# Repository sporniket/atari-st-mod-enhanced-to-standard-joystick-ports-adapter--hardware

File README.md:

# Enhanced to standard joystick ports adapter -- the hardware

> [WARNING] Please read carefully this note before using this project. It contains important facts.

Content

1. What is **Enhanced to standard joystick ports adapter -- the hardware**, and when to use it ?
2. What should you know before using **Enhanced to standard joystick ports adapter -- the hardware** ?
3. How to use **Enhanced to standard joystick ports adapter -- the hardware** ?
4. Known issues
5. Miscellanous

## 1. What is **Enhanced to standard joystick ports adapter -- the hardware**, and when to use it ?

**Enhanced to standard joystick ports adapter -- the hardware**, as the name implies, is the hardware part of an adapter
that will allow to plug into the pair of standard joystick ports of an Atari ST, a controller meant for the enhanced joystick
port, like the Atari Jaguar controller.

The Kicad 6 project details the schematic and the PCB of the adapter.

### Licence

**Enhanced to standard joystick ports adapter -- the hardware** is published under the Creative Commons CC0 license. You can find a copy of the licence there : https://creativecommons.org/publicdomain/zero/1.0/legalcode

You can copy, modify, distribute and perform the work, even for commercial purposes, all without asking permission.

**Enhanced to standard joystick ports adapter -- the hardware** is distributed in the hope that it will be useful, but WITHOUT ANY WARRANTY; without even the implied warranty of MERCHANTABILITY or FITNESS FOR A PARTICULAR PURPOSE.

### Release notes

> No releases yet

## 2. What should you know before using **Enhanced to standard joystick ports adapter -- the hardware** ?

**Enhanced to standard joystick ports adapter -- the hardware** is made using Kicad 6.

> Do not use **Enhanced to standard joystick ports adapter -- the hardware** if this project is not suitable for your project.

## 3. How to use **Enhanced to standard joystick ports adapter -- the hardware** ?

### From sources

To get the latest available work, one must clone the git repository, build and install the package.

	git clone https://github.com/sporniket/atari-st-mod-enhanced-to-standard-joystick-ports-adapter--hardware.git

Then, open the project with Kicad 6.

## 4. Known issues
See the [project issues](https://github.com/sporniket/atari-st-mod-enhanced-to-standard-joystick-ports-adapter--hardware/issues) page.

## 5. Miscellanous

### Report issues
Use the [project issues](https://github.com/sporniket/atari-st-mod-enhanced-to-standard-joystick-ports-adapter--hardware/issues) page.

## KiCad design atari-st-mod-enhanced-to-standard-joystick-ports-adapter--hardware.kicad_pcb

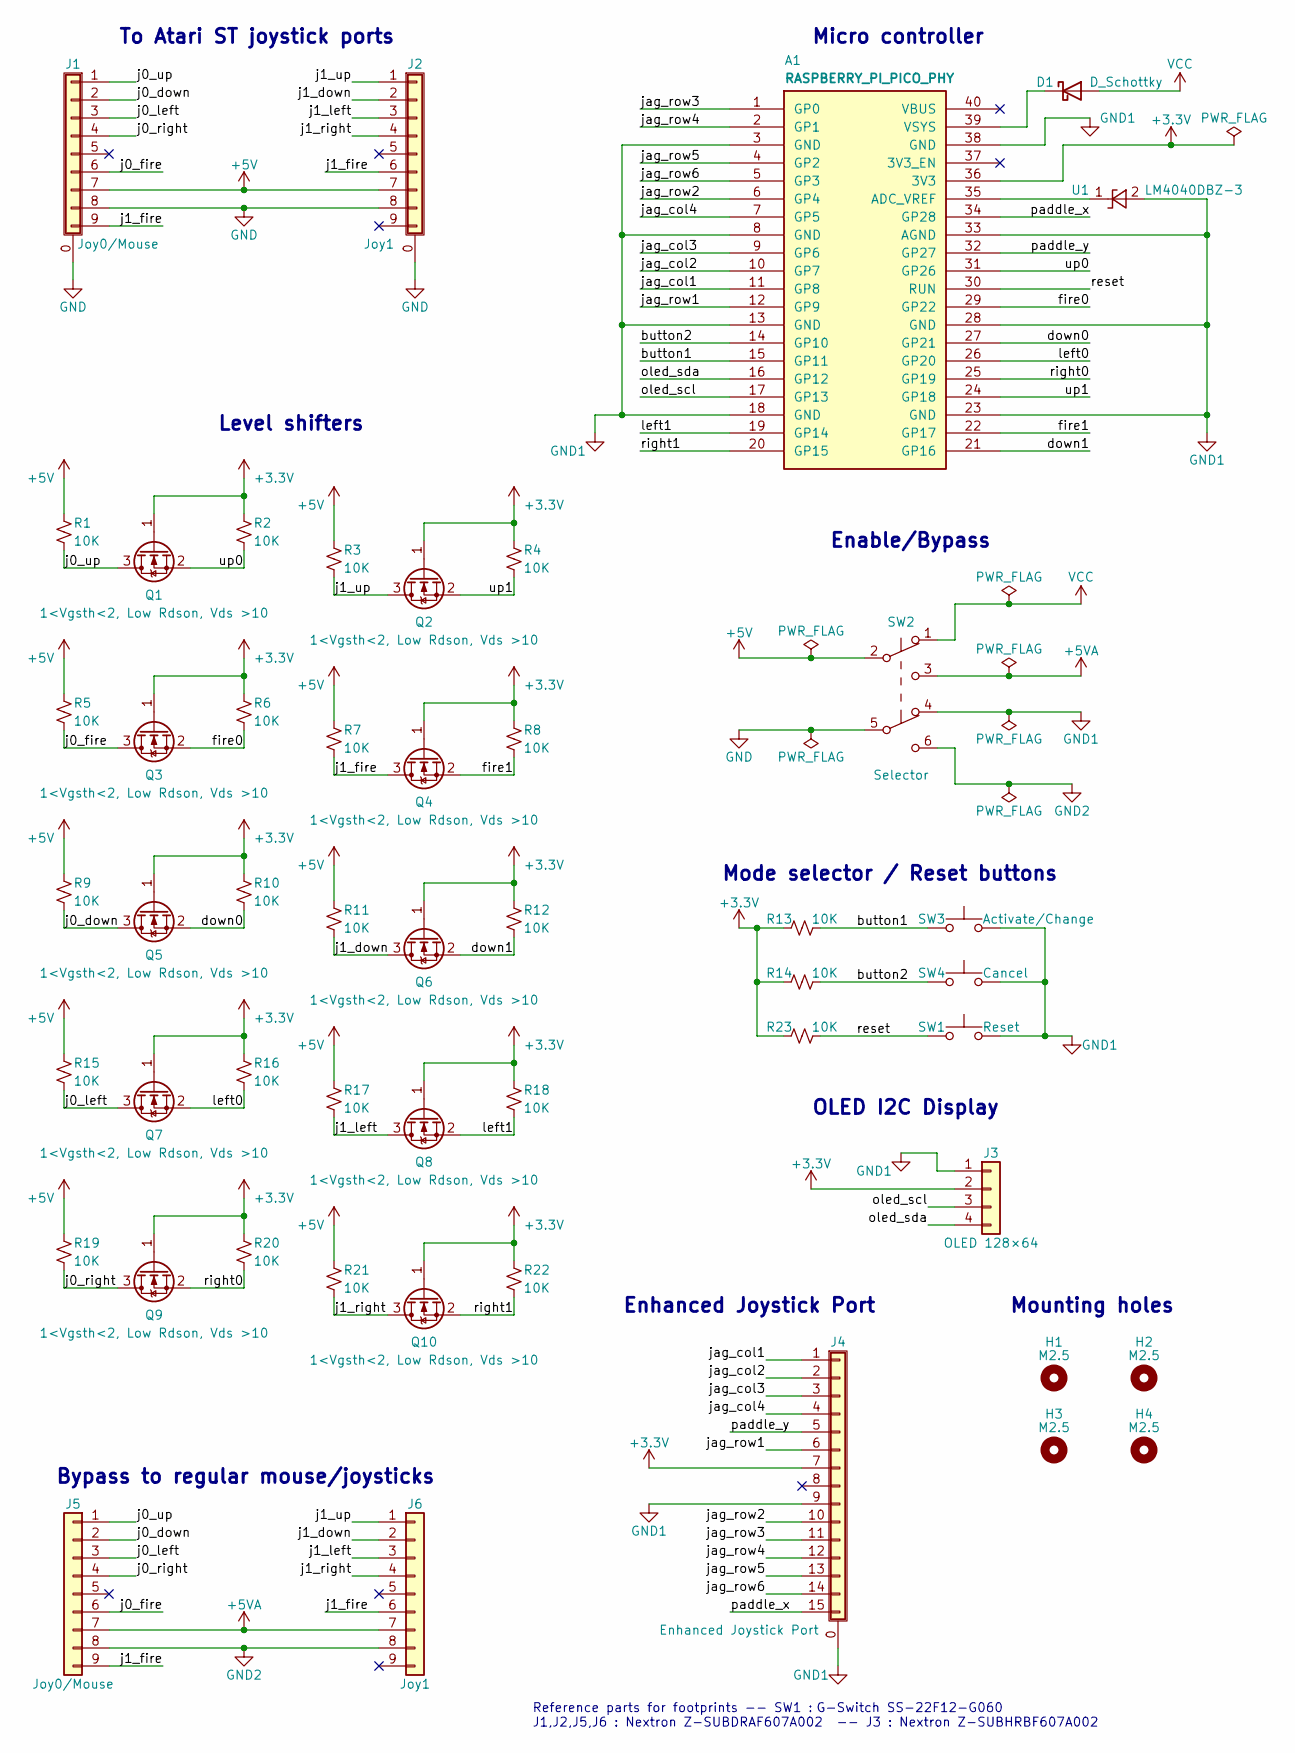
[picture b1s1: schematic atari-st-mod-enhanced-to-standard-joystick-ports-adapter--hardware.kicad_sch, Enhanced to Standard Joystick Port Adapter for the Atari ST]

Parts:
A1: RASPBERRY_PI_PICO_PHY; DIP-40_700_RASPBERRY_PI_PICO
D1: D_Schottky; D_SOD-323
H1, H2, H3, H4: M2.5; MountingHole_2.7mm_M2.5
J1: Joy0/Mouse; DSUB-9_Female_Horizontal_P2.77x2.84mm_EdgePinOffset7.70mm_H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; LCSC part number C115167
J2: Joy1; DSUB-9_Female_Horizontal_P2.77x2.84mm_EdgePinOffset7.70mm_H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; LCSC part number C115167
J3: OLED 128×64; oled_display_iic_128x64pix__outer_26.70x19.26mm__inner_21.7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
J4: Enhanced Joystick Port; DSUB-15-HD_Female_Horizontal_P2.29x1.98mm_EdgePinOffset8.35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; LCSC part number C235848
J5: Joy0/Mouse; Joystick_Port_DSUB-9_Male_Horizontal_P2.77x2.84mm_EdgePinOf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; LCSC part number C115167
J6: Joy1; Joystick_Port_DSUB-9_Male_Horizontal_P2.77x2.84mm_EdgePinOf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; LCSC part number C115167
Q1, Q2, Q3, Q4, Q5, Q6, Q7, Q8, Q9, Q10: 1<Vgsth<2, Low Rdson, Vds >10; SOT-23
R1, R2, R3, R4, R5, R6, R7, R8, R9, R10, R11, R12, R13, R14, R15, R16, R17, R18, R19, R20, R21, R22, R23: 10K; R_0805_2012Metric
SW1: Reset; SW_PUSH_6mm_H9.5mm
SW2: Selector; g-switch_22f12-gxxx; LCSC part number C2848906
SW3: Activate/Change; SW_PUSH_6mm_H13mm
SW4: Cancel; SW_PUSH_6mm_H13mm
U1: LM4040DBZ-3; SOT-23

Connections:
+3V3: A1.36 (3V3), J3.2, J4.7, Q1.1 (G), Q2.1 (G), Q3.1 (G), Q4.1 (G), Q5.1 (G), Q6.1 (G), Q7.1 (G), Q8.1 (G), Q9.1 (G), Q10.1 (G), R2.1, R4.1, R6.1, R8.1, R10.1, R12.1, R13.1, R14.1, R16.1, R18.1, R20.1, R22.1, R23.1
+5V: J1.7, J2.7, R1.1, R3.1, R5.1, R7.1, R9.1, R11.1, R15.1, R17.1, R19.1, R21.1, SW2.2 (B)
+5VA: J5.7, J6.7, SW2.3 (C)
/button1: A1.15 (GP11), R13.2, SW3.1
/button2: A1.14 (GP10), R14.2, SW4.1
/down0: A1.27 (GP21), Q5.2 (S), R10.2
/down1: A1.21 (GP16), Q6.2 (S), R12.2
/fire0: A1.29 (GP22), Q3.2 (S), R6.2
/fire1: A1.22 (GP17), Q4.2 (S), R8.2
/j0_down: J1.2, J5.2, Q5.3 (D), R9.2
/j0_fire: J1.6, J5.6, Q3.3 (D), R5.2
/j0_left: J1.3, J5.3, Q7.3 (D), R15.2
/j0_right: J1.4, J5.4, Q9.3 (D), R19.2
/j0_up: J1.1, J5.1, Q1.3 (D), R1.2
/j1_down: J2.2, J6.2, Q6.3 (D), R11.2
/j1_fire: J1.9, J2.6, J5.9, J6.6, Q4.3 (D), R7.2
/j1_left: J2.3, J6.3, Q8.3 (D), R17.2
/j1_right: J2.4, J6.4, Q10.3 (D), R21.2
/j1_up: J2.1, J6.1, Q2.3 (D), R3.2
/jag_col1: A1.11 (GP8), J4.1
/jag_col2: A1.10 (GP7), J4.2
/jag_col3: A1.9 (GP6), J4.3
/jag_col4: A1.7 (GP5), J4.4
/jag_row1: A1.12 (GP9), J4.6
/jag_row2: A1.6 (GP4), J4.10
/jag_row3: A1.1 (GP0), J4.11
/jag_row4: A1.2 (GP1), J4.12
/jag_row5: A1.4 (GP2), J4.13
/jag_row6: A1.5 (GP3), J4.14
/left0: A1.26 (GP20), Q7.2 (S), R16.2
/left1: A1.19 (GP14), Q8.2 (S), R18.2
/oled_scl: A1.17 (GP13), J3.3
/oled_sda: A1.16 (GP12), J3.4
/paddle_x: A1.34 (GP28), J4.15
/paddle_y: A1.32 (GP27), J4.5
/reset: A1.30 (RUN), R23.2, SW1.1
/right0: A1.25 (GP19), Q9.2 (S), R20.2
/right1: A1.20 (GP15), Q10.2 (S), R22.2
/up0: A1.31 (GP26), Q1.2 (S), R2.2
/up1: A1.24 (GP18), Q2.2 (S), R4.2
GND: J1.0 (Shield), J1.8, J2.0 (Shield), J2.8, SW2.5 (B)
GND1: A1.3 (GND), A1.8 (GND), A1.13 (GND), A1.18 (GND), A1.23 (GND), A1.28 (GND), A1.33 (AGND), A1.38 (GND), J3.1, J4.0 (Shield), J4.9, SW1.2, SW2.4 (A), SW3.2, SW4.2, U1.2 (A)
GND2: J5.8, J6.8, SW2.6 (C)
unnamed: A1.35 (ADC_VREF), U1.1 (K)
unnamed: A1.39 (VSYS), D1.1 (K)
VCC: D1.2 (A), SW2.1 (A)

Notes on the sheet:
To Atari ST joystick ports
Level shifters
Bypass to regular mouse/joysticks
Mounting holes
Micro controller
OLED I2C Display
Enable/Bypass
Mode selector / Reset buttons
Enhanced Joystick Port
Reference parts for footprints -- SW1 : G-Switch SS-22F12-G060 J1,J2,J5,J6 : Nextron Z-SUBDRAF607A002 -- J3 : Nextron Z-SUBHRBF607A002

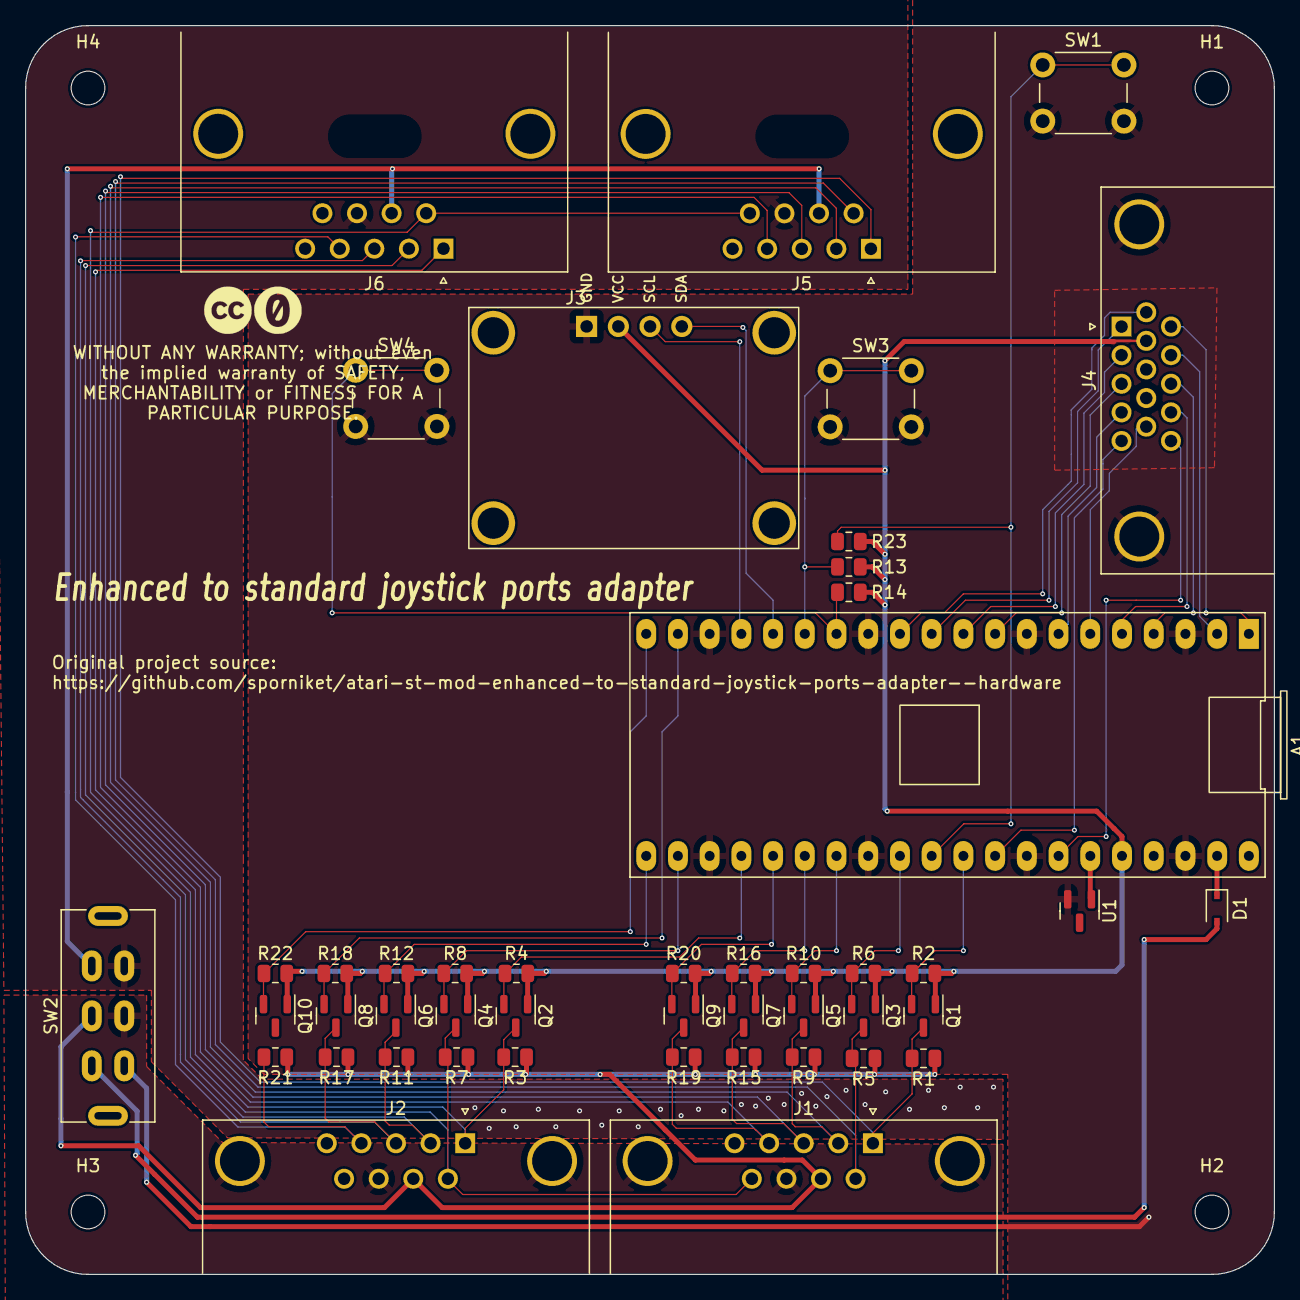
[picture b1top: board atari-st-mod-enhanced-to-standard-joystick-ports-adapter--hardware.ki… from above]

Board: 4 copper layers, 100.0 x 100.0 mm, 50 parts (0 on the bottom side), 46 nets.

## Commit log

2023-01-30 update handmade footprints
2023-01-31 added dpdt switch footprint
2023-01-31 update kicad-symbols-generated
2023-01-31 schematic done
2023-01-31 Initial README
2023-01-31 change selected connector footprint for dsub connectors
2023-02-01 rename all components, start adding LCSC parts number
2023-02-01 start pcb, assessing global size
2023-02-01 pcb : laying out in a 10x10cm square the big tht components
2023-02-02 rearrange connexion for easier routing
2023-02-07 replace basic pin header connector by proper footprint for oled screen
2023-02-08 add pull-up resistor to reset switch
2023-02-08 pcb session 2023-02-08T07:16:02+01:00
2023-02-08 pcb session 2023-02-08T21:40:26+01:00
2023-02-09 PCB session 2023-02-09T06:26:49+01:00 : title, origin, licence logos, disclaimer on silkscreen
2023-02-09 schematics : add mounting holes, shield pin 0 for connectors with metallic shields
2023-02-09 PCB session 2023-02-09T07:02:41+01:00 : mounting holes, pcb shape, 3v3 copper pour
2023-02-09 PCB session 2023-02-09T09:04:18+01:00 : copper pour work
2023-02-09 update publication date
2023-12-10 migrate to Kicad7
2023-12-10 update handmade footprints and symbol libraries
2023-12-10 change footprint of J5/J6 for plastic db9 socket
2023-12-10 pcb session 2023-12-10T09:18:17+01:00 : working on legacy joystick port
2023-12-10 cleaning the trace pathes
2023-12-10 done cleaning
